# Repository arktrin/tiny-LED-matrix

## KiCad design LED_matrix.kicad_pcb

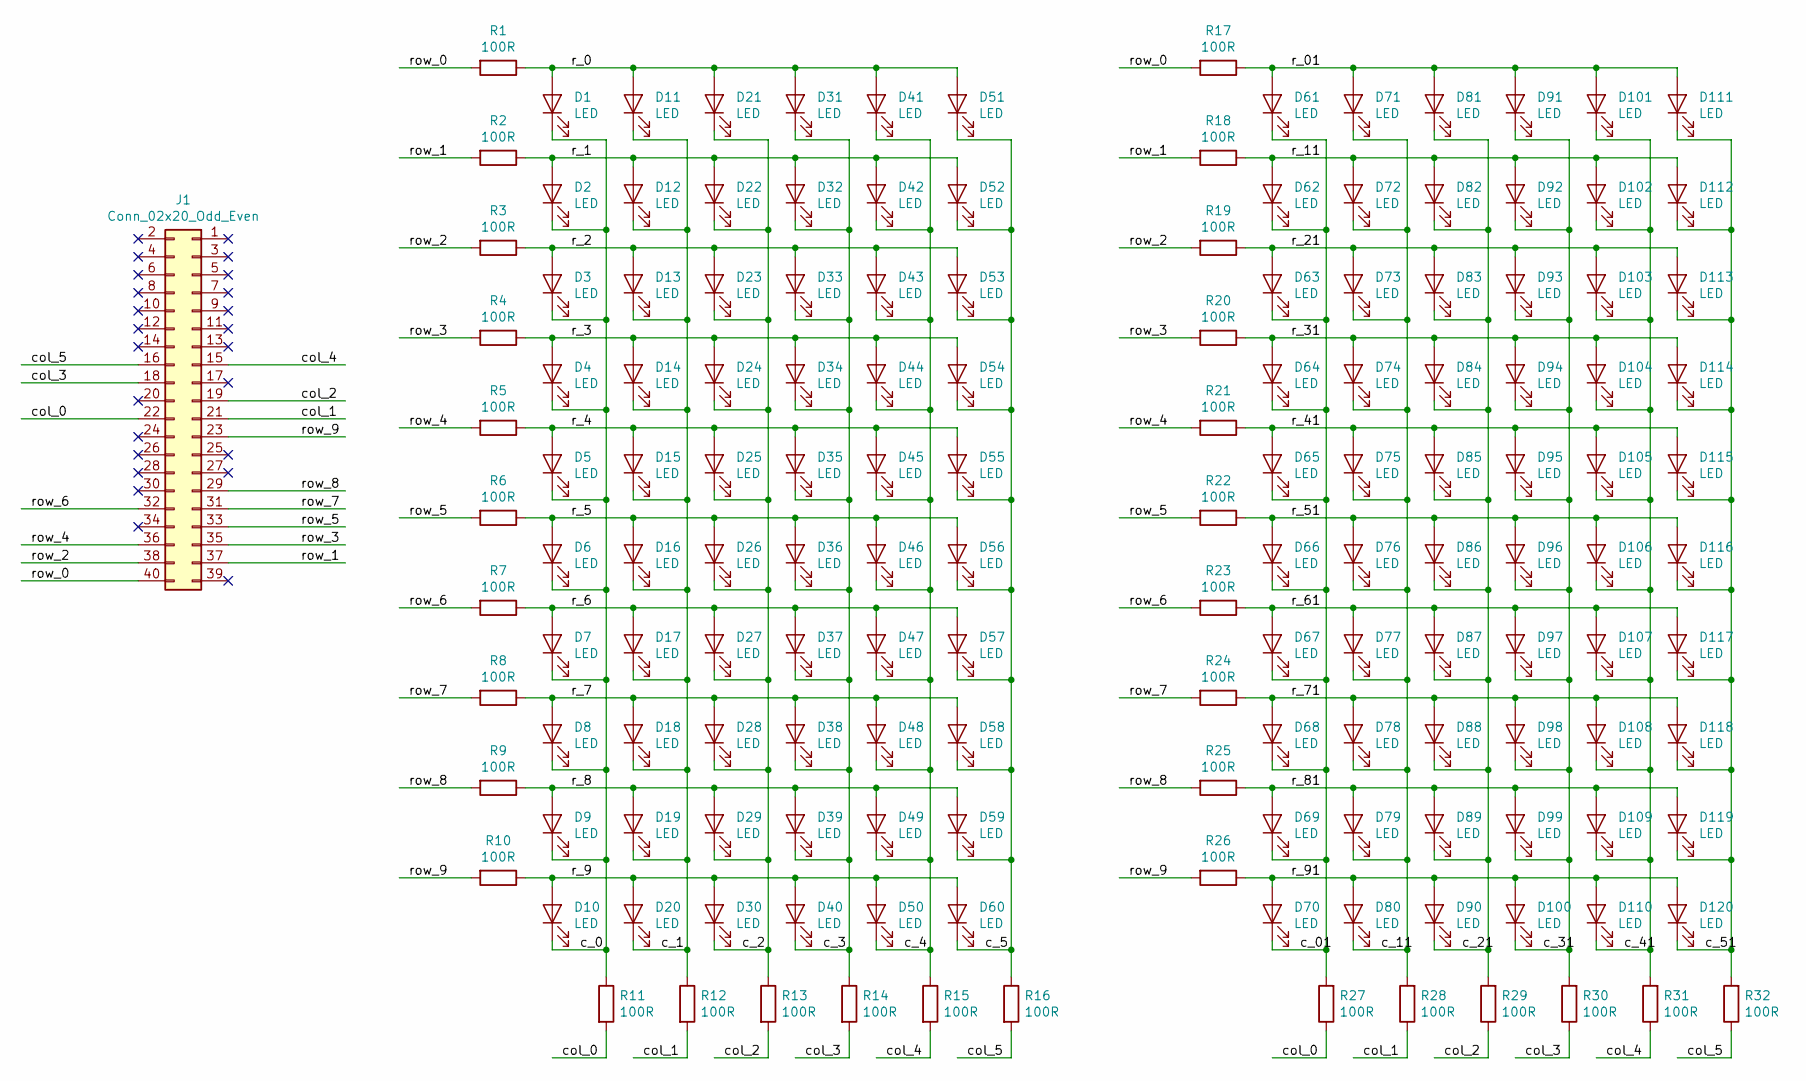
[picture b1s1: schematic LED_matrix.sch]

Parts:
D1, D2, D3, D4, D5, D6, D7, D8, D9, D10, D11, D12, D13, D14, D15, D16, D17, D18, D19, D20, D21, D22, D23, D24, D25, D26, D27, D28, D29, D30, D31, D32, D33, D34, D35, D36, D37, D38, D39, D40, D41, D42, D43, D44, D45, D46, D47, D48, D49, D50, D51, D52, D53, D54, D55, D56, D57, D58, D59, D60: LED; LED_0402_1005Metric
D61, D62, D63, D64, D65, D66, D67, D68, D69, D70, D71, D72, D73, D74, D75, D76, D77, D78, D79, D80, D81, D82, D83, D84, D85, D86, D87, D88, D89, D90, D91, D92, D93, D94, D95, D96, D97, D98, D99, D100, D101, D102, D103, D104, D105, D106, D107, D108, D109, D110, D111, D112, D113, D114, D115, D116, D117, D118, D119, D120: LED; LED_0402_round
J1: Conn_02x20_Odd_Even; PinHeader_2x20_P2.54mm_Vertical
R1, R2, R3, R4, R5, R6, R7, R8, R9, R10, R11, R12, R13, R14, R15, R16, R17, R18, R19, R20, R21, R22, R23, R24, R25, R26, R27, R28, R29, R30, R31, R32: 100R; R_0603_1608Metric

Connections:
/c_0: D1.1 (K), D2.1 (K), D3.1 (K), D4.1 (K), D5.1 (K), D6.1 (K), D7.1 (K), D8.1 (K), D9.1 (K), D10.1 (K), R11.1
/c_1: D11.1 (K), D12.1 (K), D13.1 (K), D14.1 (K), D15.1 (K), D16.1 (K), D17.1 (K), D18.1 (K), D19.1 (K), D20.1 (K), R12.1
/c_01: D61.1 (K), D62.1 (K), D63.1 (K), D64.1 (K), D65.1 (K), D66.1 (K), D67.1 (K), D68.1 (K), D69.1 (K), D70.1 (K), R27.2
/c_2: D21.1 (K), D22.1 (K), D23.1 (K), D24.1 (K), D25.1 (K), D26.1 (K), D27.1 (K), D28.1 (K), D29.1 (K), D30.1 (K), R13.1
/c_3: D31.1 (K), D32.1 (K), D33.1 (K), D34.1 (K), D35.1 (K), D36.1 (K), D37.1 (K), D38.1 (K), D39.1 (K), D40.1 (K), R14.1
/c_4: D41.1 (K), D42.1 (K), D43.1 (K), D44.1 (K), D45.1 (K), D46.1 (K), D47.1 (K), D48.1 (K), D49.1 (K), D50.1 (K), R15.1
/c_5: D51.1 (K), D52.1 (K), D53.1 (K), D54.1 (K), D55.1 (K), D56.1 (K), D57.1 (K), D58.1 (K), D59.1 (K), D60.1 (K), R16.1
/c_11: D71.1 (K), D72.1 (K), D73.1 (K), D74.1 (K), D75.1 (K), D76.1 (K), D77.1 (K), D78.1 (K), D79.1 (K), D80.1 (K), R28.2
/c_21: D81.1 (K), D82.1 (K), D83.1 (K), D84.1 (K), D85.1 (K), D86.1 (K), D87.1 (K), D88.1 (K), D89.1 (K), D90.1 (K), R29.2
/c_31: D91.1 (K), D92.1 (K), D93.1 (K), D94.1 (K), D95.1 (K), D96.1 (K), D97.1 (K), D98.1 (K), D99.1 (K), D100.1 (K), R30.2
/c_41: D101.1 (K), D102.1 (K), D103.1 (K), D104.1 (K), D105.1 (K), D106.1 (K), D107.1 (K), D108.1 (K), D109.1 (K), D110.1 (K), R31.2
/c_51: D111.1 (K), D112.1 (K), D113.1 (K), D114.1 (K), D115.1 (K), D116.1 (K), D117.1 (K), D118.1 (K), D119.1 (K), D120.1 (K), R32.2
/col_0: J1.22, R11.2, R27.1
/col_1: J1.21, R12.2, R28.1
/col_2: J1.19, R13.2, R29.1
/col_3: J1.18, R14.2, R30.1
/col_4: J1.15, R15.2, R31.1
/col_5: J1.16, R16.2, R32.1
/r_0: D1.2 (A), D11.2 (A), D21.2 (A), D31.2 (A), D41.2 (A), D51.2 (A), R1.1
/r_1: D2.2 (A), D12.2 (A), D22.2 (A), D32.2 (A), D42.2 (A), D52.2 (A), R2.1
/r_01: D61.2 (A), D71.2 (A), D81.2 (A), D91.2 (A), D101.2 (A), D111.2 (A), R17.1
/r_2: D3.2 (A), D13.2 (A), D23.2 (A), D33.2 (A), D43.2 (A), D53.2 (A), R3.1
/r_3: D4.2 (A), D14.2 (A), D24.2 (A), D34.2 (A), D44.2 (A), D54.2 (A), R4.1
/r_4: D5.2 (A), D15.2 (A), D25.2 (A), D35.2 (A), D45.2 (A), D55.2 (A), R5.1
/r_5: D6.2 (A), D16.2 (A), D26.2 (A), D36.2 (A), D46.2 (A), D56.2 (A), R6.1
/r_6: D7.2 (A), D17.2 (A), D27.2 (A), D37.2 (A), D47.2 (A), D57.2 (A), R7.1
/r_7: D8.2 (A), D18.2 (A), D28.2 (A), D38.2 (A), D48.2 (A), D58.2 (A), R8.1
/r_8: D9.2 (A), D19.2 (A), D29.2 (A), D39.2 (A), D49.2 (A), D59.2 (A), R9.1
/r_9: D10.2 (A), D20.2 (A), D30.2 (A), D40.2 (A), D50.2 (A), D60.2 (A), R10.1
/r_11: D62.2 (A), D72.2 (A), D82.2 (A), D92.2 (A), D102.2 (A), D112.2 (A), R18.1
/r_21: D63.2 (A), D73.2 (A), D83.2 (A), D93.2 (A), D103.2 (A), D113.2 (A), R19.1
/r_31: D64.2 (A), D74.2 (A), D84.2 (A), D94.2 (A), D104.2 (A), D114.2 (A), R20.1
/r_41: D65.2 (A), D75.2 (A), D85.2 (A), D95.2 (A), D105.2 (A), D115.2 (A), R21.1
/r_51: D66.2 (A), D76.2 (A), D86.2 (A), D96.2 (A), D106.2 (A), D116.2 (A), R22.1
/r_61: D67.2 (A), D77.2 (A), D87.2 (A), D97.2 (A), D107.2 (A), D117.2 (A), R23.1
/r_71: D68.2 (A), D78.2 (A), D88.2 (A), D98.2 (A), D108.2 (A), D118.2 (A), R24.1
/r_81: D69.2 (A), D79.2 (A), D89.2 (A), D99.2 (A), D109.2 (A), D119.2 (A), R25.1
/r_91: D70.2 (A), D80.2 (A), D90.2 (A), D100.2 (A), D110.2 (A), D120.2 (A), R26.1
/row_0: J1.40, R1.2, R17.2
/row_1: J1.37, R2.2, R18.2
/row_2: J1.38, R3.2, R19.2
/row_3: J1.35, R4.2, R20.2
/row_4: J1.36, R5.2, R21.2
/row_5: J1.33, R6.2, R22.2
/row_6: J1.32, R7.2, R23.2
/row_7: J1.31, R8.2, R24.2
/row_8: J1.29, R9.2, R25.2
/row_9: J1.23, R10.2, R26.2

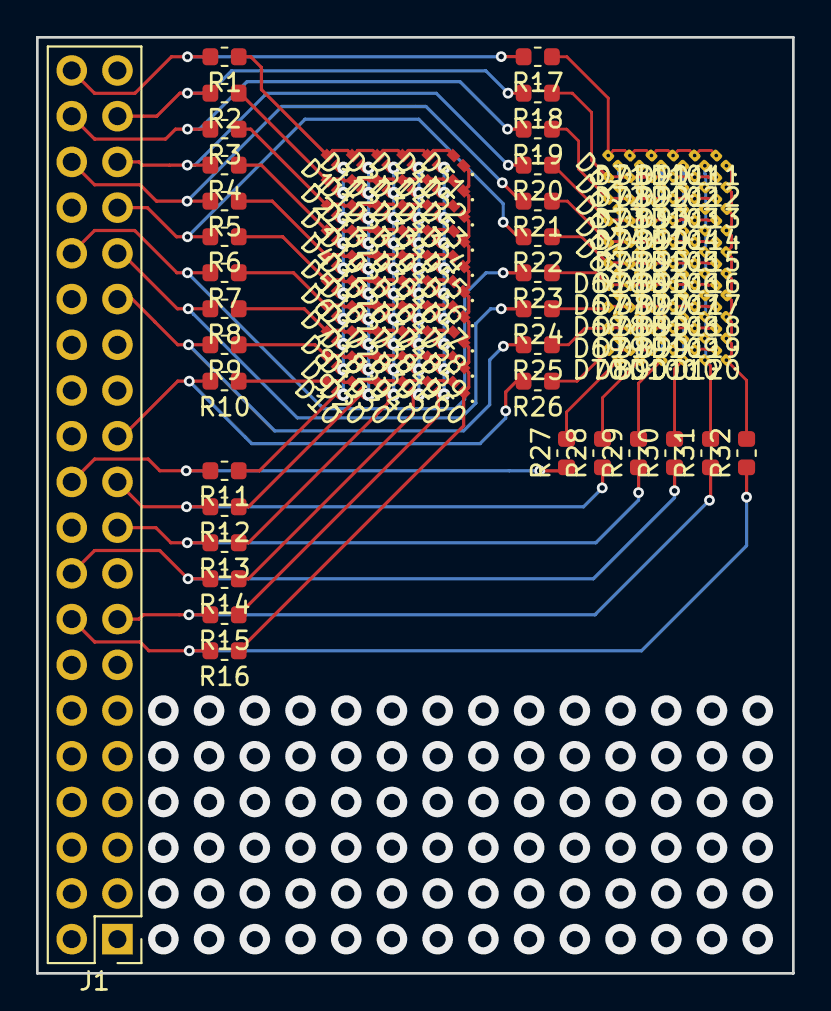
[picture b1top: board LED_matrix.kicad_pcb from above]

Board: 2 copper layers, 42.0 x 52.0 mm, 153 parts (0 on the bottom side), 48 nets.

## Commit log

2019-03-10 start adding more dense LED matrix
2019-03-11 add LED matrix with 1.2mm pitch
2019-03-11 align LEDs
2019-03-11 move to 0.2/0.5 vias
2019-03-12 generate gerber files + bugs fix
2019-03-17 add test python script
2019-03-17 test script code cleanup
2019-03-20 update test script
2019-03-21 optimize row scan + add pulsing function
